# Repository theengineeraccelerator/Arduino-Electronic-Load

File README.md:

# Arduino-Electronic-Load

test

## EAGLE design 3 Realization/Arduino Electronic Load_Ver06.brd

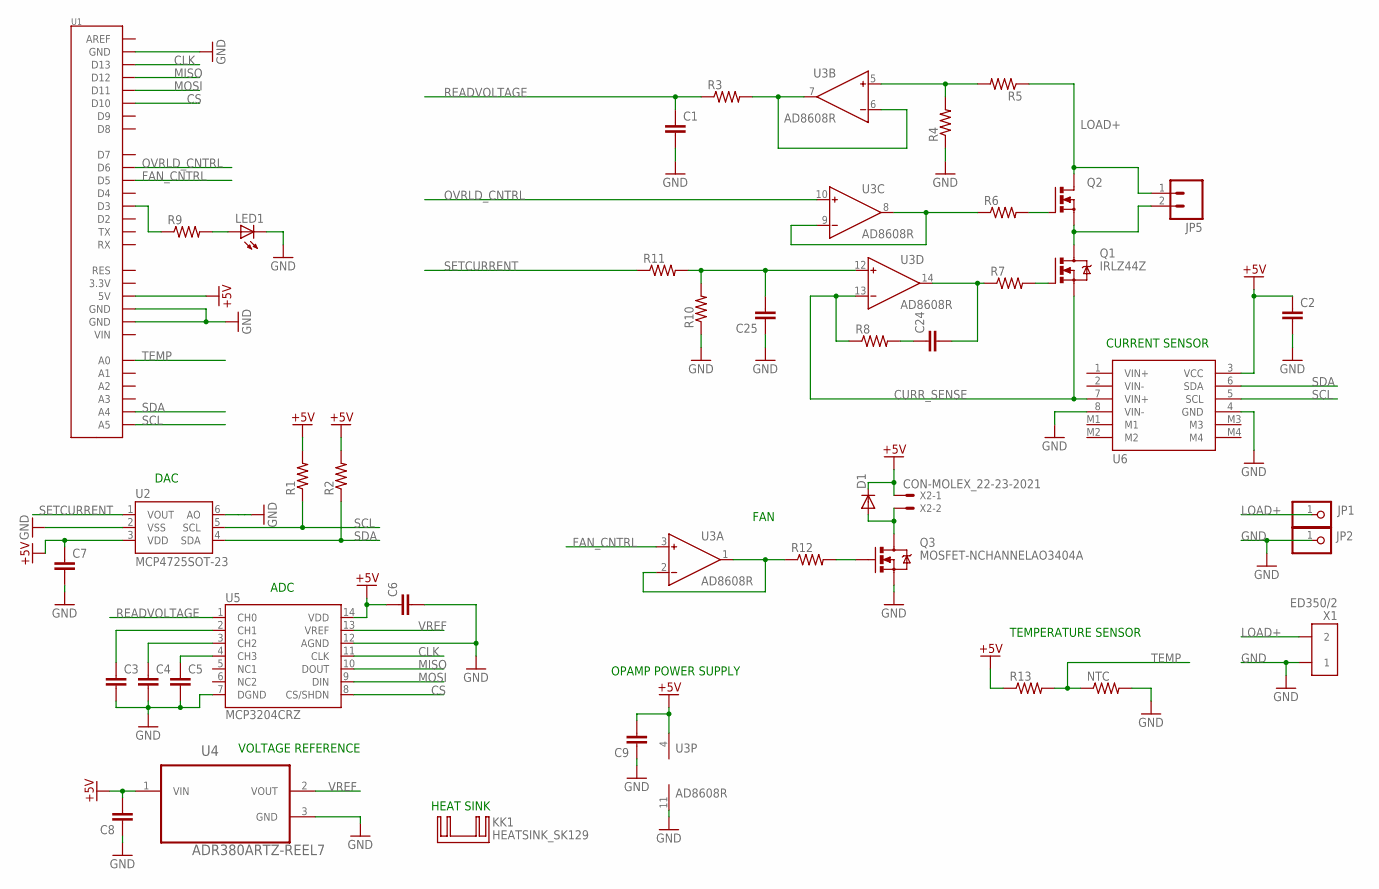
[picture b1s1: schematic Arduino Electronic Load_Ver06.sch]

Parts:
C1, C2, C3, C4, C5, C6, C7, C8, C9, C24, C25: CAP0603-CAP; 0603-CAP
D1: DIODEPTH; DIODE-1N4001
JP1, JP2: PINHEAD_PINHD-1X1; PINHEAD_1X01
JP5: M02; 1X02_LONGPADS
KK1: HEATSINK_SK129; HEATSINK_SK129-HOLE
LED1: LED5MM
NTC: RESISTOR0402-RES; 0402-RES
Q1: IRLZ44Z; TO220BV_1
Q2: PMOSFET_NTO220BV; TO220BV
Q3: MOSFET-NCHANNELAO3404A; SOT23-3
R1, R2, R3, R4, R5, R6, R7, R8, R9, R10, R11, R12, R13: RESISTOR0603-RES; 0603-RES
U1: ARDUINO_SHIELD; DUEMILANOVE_SHIELD
U2: MCP4725SOT-23; SOT23-6
U3: AD8608R; SO14
U4: ADR380ARTZ-REEL7; SOT95P237X112-3N
U5: MCP3204CRZ; SOIC-14
U6: INA219
X1: ED350/2
X2: CON-MOLEX_22-23-2021

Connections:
+5V: C2.1, C6.1, C7.1, C8.2, C9.2, D1.C, R1.2, R2.2, R13.1, U1.5V, U2.3 (VDD), U3.4 (V+), U4.1 (VIN), U5.14 (VDD), U6.3 (VCC), X2.1
CLK: U1.D13, U5.11 (CLK)
CS: U1.D10, U5.8 (CS/SHDN)
CURR_SENSE: Q1.S, R8.1, U3.13 (IN-), U6.7 (VIN+)
FAN_CNTRL: U1.D5, U3.3 (IN+)
GND: C1.2, C2.2, C3.2, C4.2, C5.2, C6.2, C7.2, C8.1, C9.1, C25.1, JP2.1, LED1.K (C), NTC.2, Q3.2 (S), R4.1, R10.1, U1.GND@0 (GND), U1.GND@1 (GND), U1.GND@2 (GND), U2.2 (VSS), U2.6 (AO), U3.11 (V-), U4.3 (GND), U5.7 (DGND), U5.12 (AGND), U6.4 (GND), U6.8 (VIN-), X1.P$1 (1)
LOAD+: JP1.1, JP5.1, Q2.D, R5.1, X1.P$2 (2)
MISO: U1.D12, U5.10 (DOUT)
MOSI: U1.D11, U5.9 (DIN)
unnamed: R9.1, U1.D3
unnamed: LED1.A, R9.2
unnamed: R12.1, U3.1 (OUT), U3.2 (IN-)
unnamed: Q3.1 (G), R12.2
unnamed: C3.1, U5.2 (CH1)
unnamed: R3.2, U3.6 (IN-), U3.7 (OUT)
unnamed: R6.1, U3.8 (OUT), U3.9 (IN-)
unnamed: R4.2, R5.2, U3.5 (IN+)
unnamed: Q2.G, R6.2
unnamed: JP5.2, Q1.D, Q2.S
unnamed: Q1.G, R7.2
unnamed: C24.2, R7.1, U3.14 (OUT)
unnamed: C4.1, U5.3 (CH2)
unnamed: C24.1, R8.2
unnamed: C5.1, U5.4 (CH3)
unnamed: C25.2, R10.2, R11.2, U3.12 (IN+)
unnamed: D1.A, Q3.3 (D), X2.2
OVRLD_CNTRL: U1.D6, U3.10 (IN+)
READVOLTAGE: C1.1, R3.1, U5.1 (CH0)
SCL: R1.1, U1.A5, U2.5 (SCL), U6.5 (SCL)
SDA: R2.1, U1.A4, U2.4 (SDA), U6.6 (SDA)
SETCURRENT: R11.1, U2.1 (VOUT)
TEMP: NTC.1, R13.2, U1.A0
VREF: U4.2 (VOUT), U5.13 (VREF)

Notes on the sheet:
DAC
ADC
VOLTAGE REFERENCE
CURRENT SENSOR
HEAT SINK
OPAMP POWER SUPPLY
FAN
TEMPERATURE SENSOR

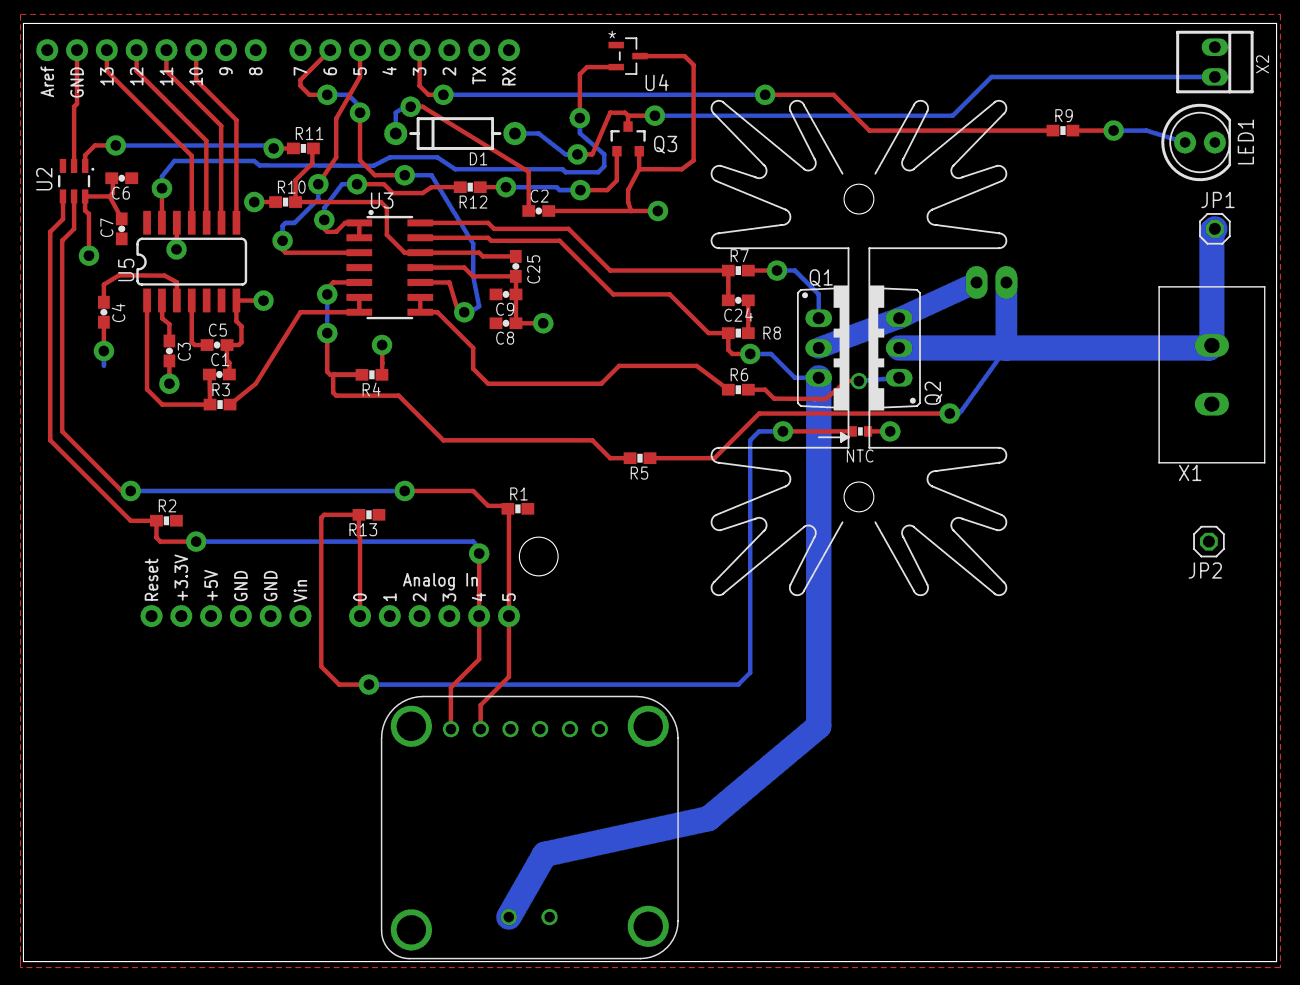
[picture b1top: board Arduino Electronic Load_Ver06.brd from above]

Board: 2 copper layers, 106.9 x 80.0 mm, 42 parts (0 on the bottom side), 33 nets.

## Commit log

2017-09-23 Inital Upload
2017-09-23 test
2017-09-27 Flow Diagram
2017-09-27 Revert "First Draft Block Diagram"
2017-09-29 Added Comments to Flow Diagram
2017-10-05 Clean , upgrade and added product definition folder
2017-10-10 Major BOM Added and old documntes from Archiucture folder archived
2017-10-17 Architecture- Hardware Block Diagram and Full Component BOM added
2017-10-25 Product Definition and Hardware Block Diagram Completed
    Comments considered and corrections are made.
2017-10-25 Full Component BOM Updated
    Full Component BOM, both the Major components sheet and Additional Components Sheet updated based on the comments received
2017-11-01 Feed Back Corrections Included
    Product definition, Hardware Block Diagram and Full Component BOM is corrected as per the feedback.
    A pageshot of the STATE MACHINE is also incuded for further comment
